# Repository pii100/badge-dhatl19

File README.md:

# badge-dhatl19

A basic indie badge desinged for dreamhack atl 2019

Features:
TFT SPI screen with touch and SD card
24x ws2812b neopixles
esp-32 for bluetooth and wifi
  
Badge is desinged to attach to a lanyard with the legit event badge below

Firmware/Software will live in a seperate repo [Link]

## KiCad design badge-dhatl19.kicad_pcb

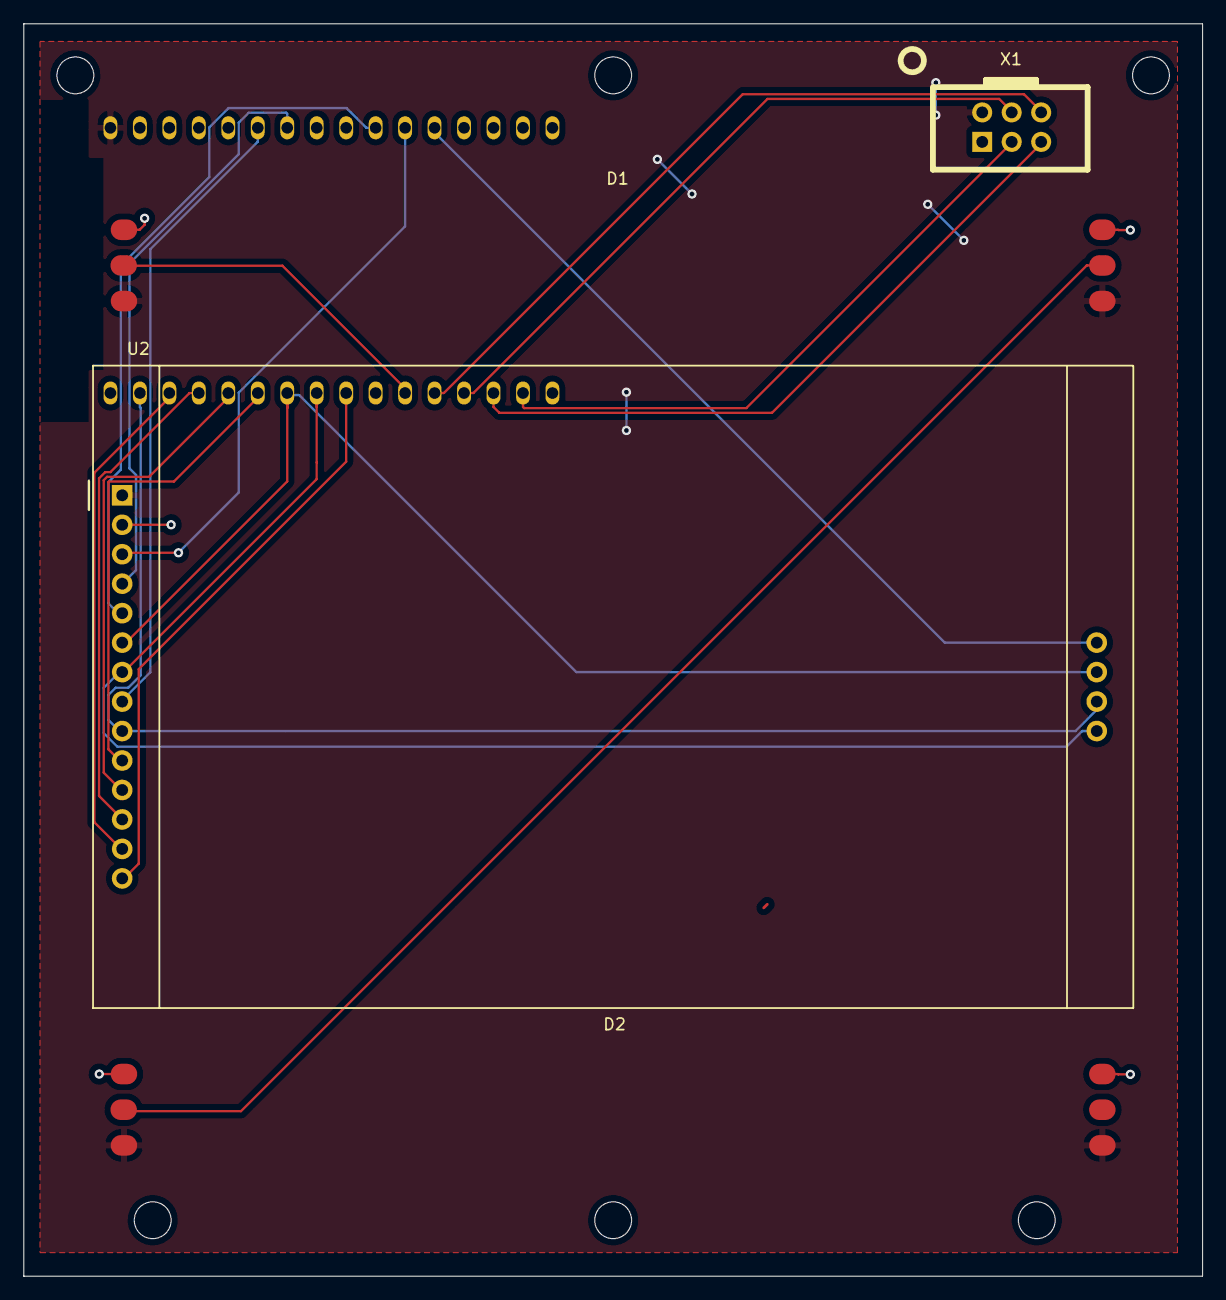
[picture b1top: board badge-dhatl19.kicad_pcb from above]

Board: 2 copper layers, 101.6 x 107.9 mm, 5 parts (1 on the bottom side), 21 nets.

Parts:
D1, D2: ws2812strip12x
U1: LolinD32_pro
U2: ili9341_3.2_touch_sd
X1: Badgelife_sao_connector_v169bis; Badgelife-SAOv169-BADGE-2x3

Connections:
+3V3: D1.3, D1.4, D2.3, D2.4, U1.1, U2.1, X1.1
/DISPLAY_CS: U1.11, U2.3
/DISPLAY_DC: U1.10, U2.5
/DISPLAY_LED: U1.6, U2.8
/DISPLAY_MISO: U1.31, U2.9, U2.17
/DISPLAY_MOSI: U1.26, U2.6, U2.16
/DISPLAY_RST: U1.7, U2.4
/DISPLAY_SCK: U1.25, U2.7, U2.18
/DISPLAY_T_CLK: U1.27, U2.10
/DISPLAY_T_CS: U1.28, U2.11
/DISPLAY_T_DIN: U1.29, U2.12
/DISPLAY_T_DO: U1.30, U2.13
/DISPLAY_T_IRQ: U1.24, U2.14
/RGB_DIN1: D1.2, U1.22
/SAO_GPIO1: U1.21, X1.5
/SAO_GPIO2: U1.19, X1.6
/SAO_SCL: U1.18, X1.4
/SAO_SDA: U1.20, X1.3
/SD_CS: U1.12, U2.15
GND: D1.1, D1.6, D2.1, D2.6, U1.17, U2.2, X1.2
unnamed: D1.5, D2.2

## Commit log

2019-10-14 cleanup
2019-10-15 added custom display library and footprint
2019-10-15 removed dead datasheet link from symbol
2019-10-15 added symbol library table
2019-10-15 added symbol datasheet link
2019-10-15 updated symbol in schematic
2019-10-15 added net names in schematic
2019-10-15 updated led and esp position
2019-10-15 board routing for display nets
2019-10-15 creating custom components
2019-10-24 added SAO
2020-01-17 added lolin d32 footprint and symbol
2020-01-17 added strip upated ref on lolin
2020-01-17 fixed pins
2020-01-17 updated schematic and pcb
2020-01-17 updated pcb
2020-01-20 added display footprint and routed board
2020-01-20 fixed u1 ref
